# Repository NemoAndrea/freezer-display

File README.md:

A common situation you find in wetlabs around the world is that there are many samples, but it is not easy to keep track of where they may be in the many freezers. Solutions generally come in two flavours:

1. A crumpled piece of damp printerpaper, covered in unreadable scribbles and crossed-out old sample labels that (allegedly) lists the contents of the freezer.
2. An online system that is well organised, but requires loading a webpage on a prehistoric netbook, setting you back 4 minutes before you finally get the information you need.

This Open Hardware design aims to provide a relatively affordable solution that aims to improve the Freezer organisation experience for those managing their Freezers with some kind of electronic system. It displays the fridge contents on an Electronic Paper Display (E-ink), and updates itself. 

This way you not only have the advantage of having a well organised online freezer system, but **also** the advantage of having that information as **immediately available** as that outdated unreadable piece of paper that used to be on the fridge. Nobody wants a crusty piece of paper with hieroglyphics, and nobody wants to spend 3 minutes on the world's slowest computer just to find out where sample X is supposed to be stored. This solution keeps the best of both worlds.

### Hardware & Assembly

The hardware design files, [BOM](enclosure/BOM_freezer-display-assembly.csv) and assembly instructions can be found in the [enclosure](enclosure/) directory. 

Note that the device is not battery powered. 

### Software & Flashing

The code/firmware for this project can be found in the [esp](esp/) directory. The project uses the Espressif development toolchain to manage the c/c++ firmware. There you will also find instructions on the setup and on how to flash the device.

### Contributing

If you want to modify the project, I strongly suggest you use the git hooks provided in the .githooks directory. They will ensure you will always commit the most recent version of FreeCAD files and derivative items (step files, thumbnails).

```bash
git config --local core.hooksPath .githooks/
```

### Some possible future upgrades

The chosen hardware has a room for future improvements and additional functionality. In no particular order, these are some low-hanging fruit improvements.

* Add small battery, and optimise for low-power use.
* Landscape/portrait mode switching and sensor to sense this directly
* Some capacitive buttons (no ingress point, can use capacitive button pins on ESP32)
* Proper weather (or in this case Lab Goo™) sealing on the USB port
* NFC functionality to allow users to update the panel with a tap of their phone/lab device 

### Funding & Acknowledgements

This project was developed for and funded by the lab of Marileen Dogterom at the TU Delft.

Contributors:
* Nemo Andrea 

# Nix related

Use https://github.com/mirrexagon/nixpkgs-esp-dev for a shell that will enable development.

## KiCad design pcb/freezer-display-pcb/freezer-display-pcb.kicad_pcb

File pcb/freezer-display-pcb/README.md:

# Shim PCB

The PCB for the project is a simple shim PCB, i.e. it merely serves to connect the two boards, functioning as a low-profile connector. Since we are severely constrained in terms of space, and we don't have control over the connectors on the boards that we are connecting, this seems like the best solution.

To assemble the PCB stack, you will need to remove some headers from the Waveshare board:

1. the 13 pin single row header
2. The 40-pin female Raspberry Pi-compatible header.
3. The 6-pin connector that is used for non-raspberry boards. 

The shim PCB will solder to the contact of connector 3. 

> [!TIP]
> You can temporarily add a M2.5 bolt and nut to keep the boards together and in the correct orientation during soldering. Note that the bolt will need to be removed in the final assembly.

### PCB Manufacturing notes

I had my boards manufactured at Aisler. Any board manufacturer that can do castellated edges should be fine. I would opt for a standard thickness. 

> [!IMPORTANT]
> The board must be manufactured with castellated edges.

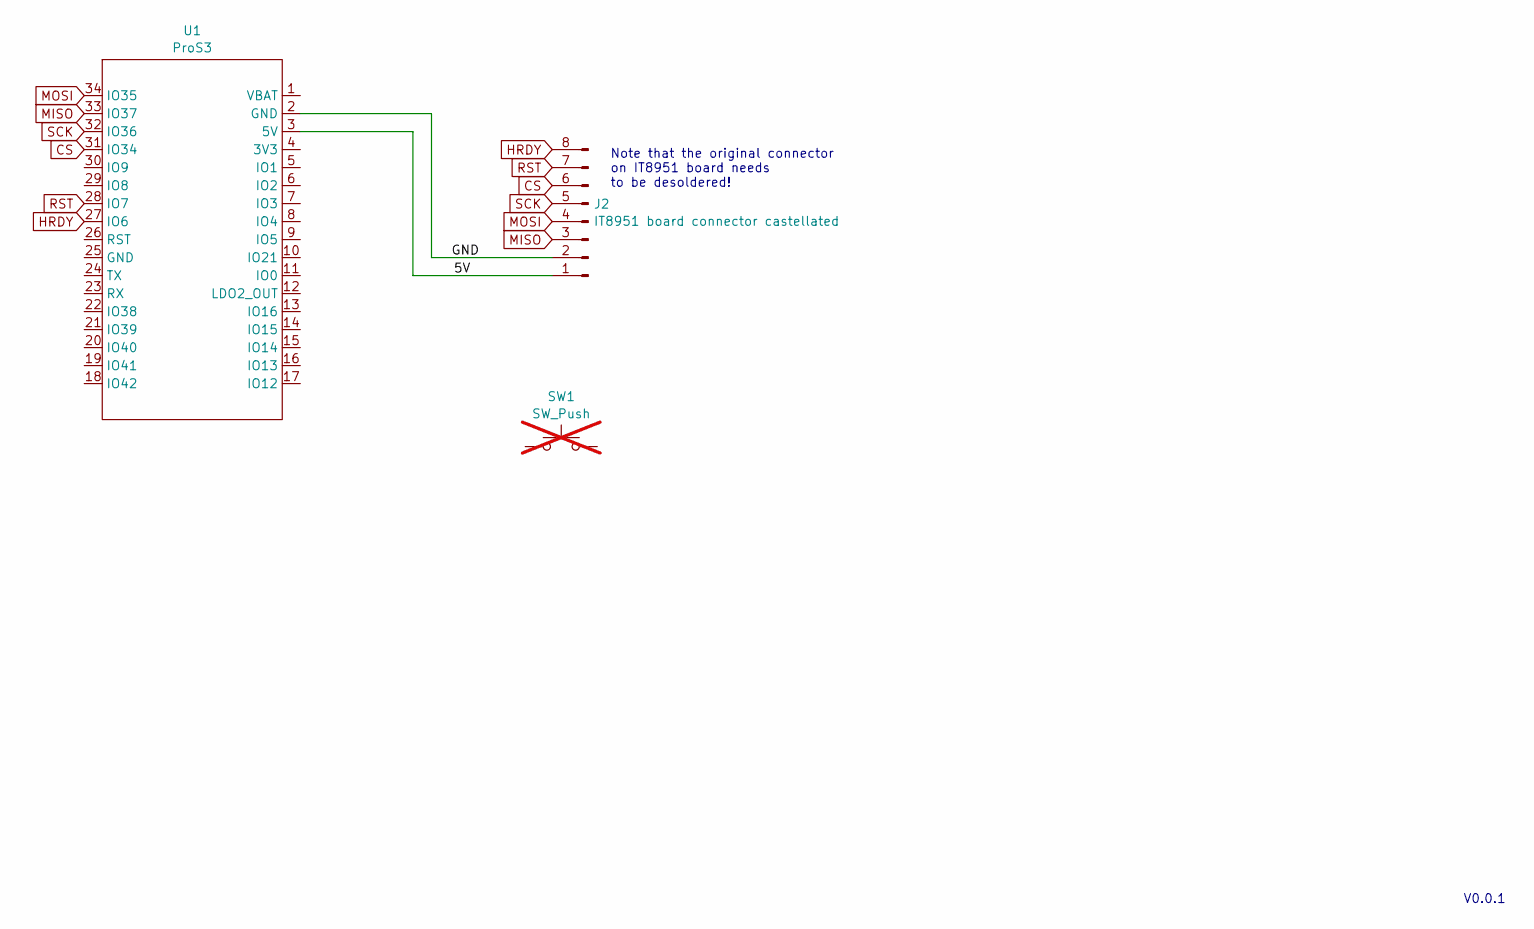
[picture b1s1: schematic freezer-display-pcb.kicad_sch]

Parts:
J2: IT8951 board connector castellated; IT8951-diver-castellated
SW1: SW_Push; SW_Tactile_SPST_Angled_PTS645Vx83-2LFS; Mouser 506-2-1825027-0; not fitted
U1: ProS3; ProS3_SMD

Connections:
/5V: J2.1, U1.3 (5V)
/GND: J2.2, U1.2 (GND)
CS: J2.6, U1.31 (IO34)
HRDY: J2.8, U1.27 (IO6)
MISO: J2.3, U1.33 (IO37)
MOSI: J2.4, U1.34 (IO35)
RST: J2.7, U1.28 (IO7)
SCK: J2.5, U1.32 (IO36)

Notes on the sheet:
V0.0.1
Note that the original connector on IT8951 board needs to be desoldered!

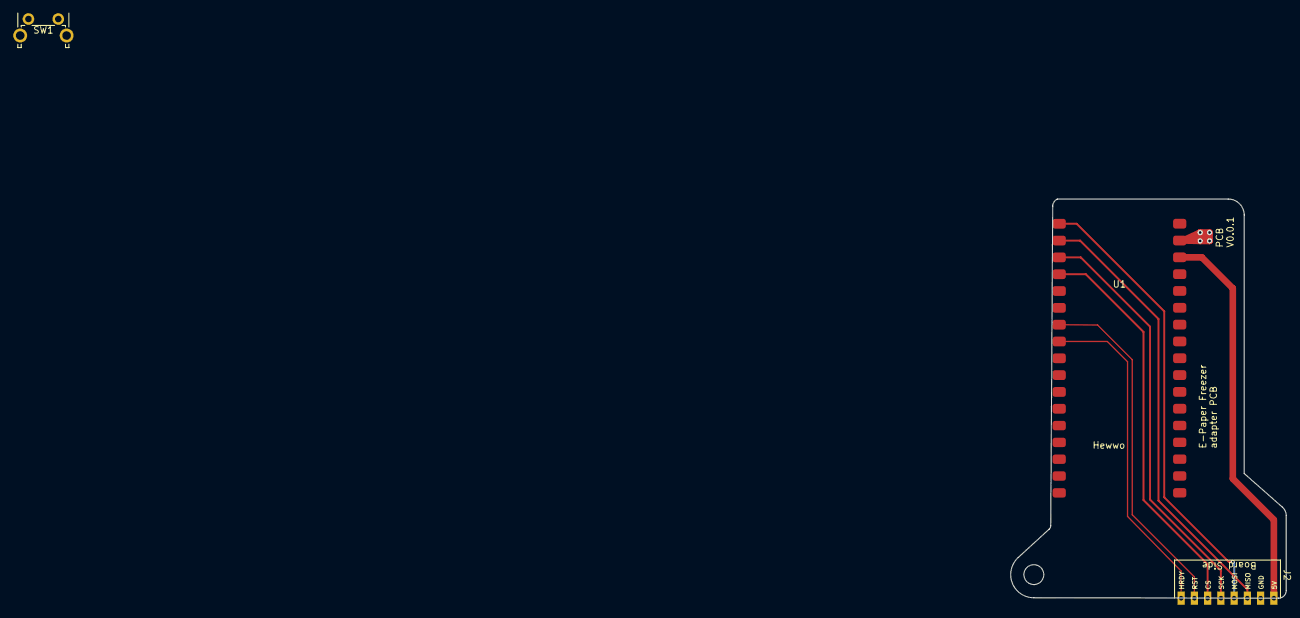
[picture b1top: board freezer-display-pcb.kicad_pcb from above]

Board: 2 copper layers, 41.6 x 60.3 mm, 3 parts (0 on the bottom side), 8 nets.

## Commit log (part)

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2024-04-04 Add simple script to simplifiy management of code
    Since we cannot instantiate git on the microcontroller drive, we simply copy the code over to the location of the repository on your main system.
2024-04-04 basic data fetching code
2024-05-03 Add dev instructions
    Added some information to main markdown
2024-05-08 Intial SPI communication code
2024-05-08 remove old file in preparation for submodule
2024-05-09 working code that refreshes the display
    turns out the main usb supply to microcontroller does not have enough power to reset the display or something like that. Unfortunate.
2024-05-09 Remove ghost files
    Accidentally commited these old files
2024-05-10 Add bitmap assets
    Added pgn and derived BMP assets that are used for the UI. Added a way to quickly convert them for windows users; linux approach still pending.
2024-05-10 Add basic bitmap UI code
    Started design of the freezermonitor class, and added implementation (still some issues regarding SPI transmission and some missing pixles) for bitmap images that can be used for the UI.
2024-05-10 Add LICENSE
    Add Licences. Software: MIT, Hardware: CERN-OHL-W-2.0
2024-05-10 fix readme
2024-05-10 Bump submodule to correct commit
2024-05-11 Add components for enclosure design and early concept
    Add 3D models for the components that go into the enclosure deisng and make a rough early concept for the enclosure. Added the ProS3 board as a submodule for footprints, 3D model and provenance.
2024-05-12 New enclosure design
    New design that involves around polycarbonate-all-around for sealing and cleanability Early work on PCB design.
2024-05-12 Add shim PCB
    Simple PCB that takes the role of low-profile wiring. In theory future buttons and LEDs could be added, but will not be considered for now.
2024-05-12 First version of complete design
    Design complete in priciple except for absence of magnet spots. Will probably still need some revisions and test prints to get everything dialed in.
2024-05-14 Increased tolerances on parts & minor tweaks
    Increased tolerances on parts, added groove for FPC cable bulk and made FPC groove 1mm wider. All based on 3D printed testfit.
2024-06-09 Fixed swapped net labels
    MISO and MOSI nets were swapped, but the functionality of the PCB was correct. Now updated to avoid confusion. PCB design has been assembled and seems to work. Added basic documentation for the PCB.
2024-06-09 Move vector designs to Inkscape
    To improve interoperatbility and customisability, the vector graphics work is now done in Inkscape (from Affinity Designer before). Should make it easier for anyone to adopt the project for their own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
2024-06-18 Adjust enclosure dimensinos to minimise cable stress
    Old design files put a lot of stress on FPC which should be avoided.
2024-06-23 Redo enclosure design to avoid backside screws
    Redid the enclosure design to avoid having screws protrude from the back; which would require stronger magnets than strictly needed. Now threaded inserts are put into the acrylic backpanel, allowing 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
2024-06-23 Remove legacy designs
    Some older design iterations were still part of the document. Removed them for clarity
2024-10-27 Minor design changes
    Archive changes made to the dockless before moving onto the design involving a static dock
2024-10-29 Add new dock-based design
2024-11-09 Add final revisions for dock based design
2024-11-09 Add 3M bumpon friction pad design file
    A simple design file for product available in the 3M SJ5300 BL Bumpon mini-pack
2024-11-09 3D printed backpanel design
    First steps towards printed backside panel (as opposed to lasercut)
2024-11-21 Improve mechanical rigidity
    Added two extra screws on the side of the frame to aid with rigidity. Added some cutout pockets in the frontpanel for the backpanel to slot into - to prevent the backpanel from flexing too much. Also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
2026-06-11 update main README for mode to linux development
2026-06-12 Work on asset .bmp production
    Automated the production of .bmp files from inkscape files. Will move away from all affinity designs in the future.
2026-06-12 Commit project state prior to move to C-based code
2026-06-20 Add skeleton esp project with required components
    Based on Espressif hello_world example scaffolding. COmmit the sdkconfig for now.
2026-06-20 Move to c++ to reproduce example from IT8951 code
2026-06-21 Reproduce demo code IT8951
    Working reproduction of https://github.com/pvginkel/it8951-esp32. It seems like GPIO pin 35 is damaged on my board. Switching a bypass wire from GPIO 4->35 reproduces expected behaviour from example 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
2026-06-22 First somewhat functional LVGL code
    Things are drawn to display after migrating sample code of Pieter van Ginkel to LVGL 9, but there are still clear artifacts. WIll move to PSRAM.
2026-06-22 Rewritten display code
    Still suffers from an internally rotation mismatch between panel and LVGL
2026-06-23 Revert to LVGL 8.0
    Reverting to LVGL 8.0 results in proper behaviour of the display. I cannot get it to work on LVGL 9.0 and don't really see the need to move to 9.0. For now the display is working, but the .c format i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
2026-06-23 remove old micropython display driver submodule
2026-06-23 Remove old micropython related files and tooling
2026-06-23 Implement WIFI and networking checks
    Add a WifiManager which checks connection to router, internet connectivity and runs it on the watchdog task. Had to move the display buffer to PSRAM to have enough internal memory for the new TLS and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
2026-06-23 Add functional eLabJournal API parsing and Freezer struct and half-functional grid display
    Added API calling and JSOn parsin of the eLabJournal API which yields a freezer struct. There are still some issues that after many loops the watchdog timer gets upset. Some memory or reference issue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
2026-06-23 Split functionality into different files and streamline startup sequence
    Split all the different functionality into different code to make it more intelligible. Streamlined the startup to have the splash screen drawn earlier on, and have the API fetching begin straightawa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
2026-06-29 Create custom partition file
    Too many libraries and assets make the main image too big. Increased partition size to accomodate (plenty of flash storage left)
2026-06-29 Add dummy freezerbox and change Box to handle parsing content string
    Split the FreezerBox construct into
2026-06-29 Large UI update for freezercontent ui
    Split each drawer into two visual compartments. Handle identical owners. Add a funtional header wiht version, api and time info. Added timezone handling.
2026-06-30 Fix issue with JSON sorting
    JSON sorting did not actually resort the indices, resulting in incorrect order of drawers if API did not supply boxes in order. Has now been corrected.
2026-06-30 Update drawer styling with improved margins and use 'owner' line also as useful space
    Per suggestion by Yash Jawale, the drawing script now also uses the first line to draw the contents of the fridge.
2026-06-30 Implement error screens
    Add somewhat useful error screens to the system.
